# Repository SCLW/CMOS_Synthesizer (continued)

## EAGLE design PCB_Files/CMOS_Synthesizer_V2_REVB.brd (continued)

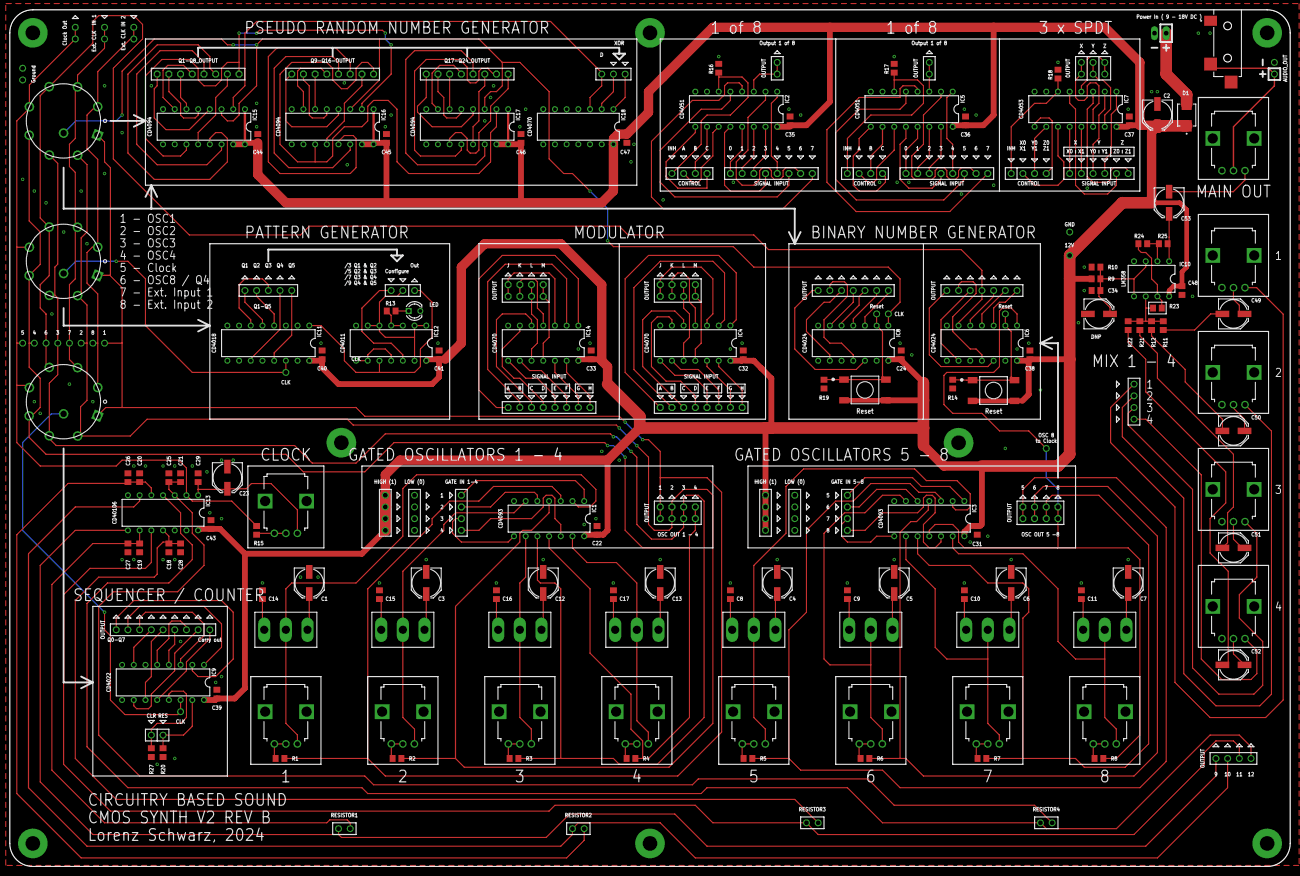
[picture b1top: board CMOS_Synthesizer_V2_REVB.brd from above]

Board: 2 copper layers, 278.0 x 186.0 mm, 218 parts (0 on the bottom side), 214 nets.

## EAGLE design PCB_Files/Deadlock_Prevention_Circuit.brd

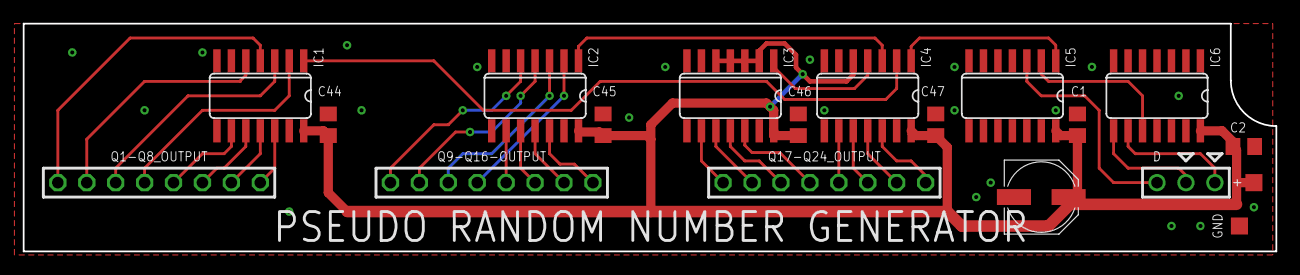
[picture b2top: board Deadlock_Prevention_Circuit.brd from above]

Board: 2 copper layers, 110.0 x 20.0 mm, 20 parts (0 on the bottom side), 34 nets.

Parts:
12V: TPTP15SQ; TP15SQ
C1, C2, C44, C45, C46, C47: 0.1uF; C0805
C3: PANASONIC_D
DATA_IN: 1X01
GND: TPTP15SQ; TP15SQ
IC1, IC2, IC3, IC4: 4068D; SO14
IC5: 4070D; SO14
IC6: 4077D; SO14
JP2: 1X02
Q1-Q8_OUTPUT, Q9-Q16-OUTPUT, Q17-Q24_OUTPUT: 1X08

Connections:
+12V: 12V.TP, C1.1, C2.1, C3.+, C44.1, C45.1, C46.1, C47.1, IC1.14, IC2.14, IC3.2, IC3.3, IC3.4, IC3.5, IC3.14, IC4.5, IC4.14, IC5.14, IC6.14
GND: C1.2, C2.2, C3.-, C44.2, C45.2, C46.2, C47.2, GND.TP, IC1.7, IC2.7, IC3.7, IC4.7, IC5.5, IC5.6, IC5.7, IC5.8, IC5.9, IC5.12, IC5.13, IC6.1, IC6.2, IC6.5, IC6.6, IC6.7, IC6.12, IC6.13
unnamed: IC1.12, Q1-Q8_OUTPUT.8
unnamed: IC6.9, JP2.1
unnamed: IC1.1, IC4.2
unnamed: IC2.1, IC4.3
unnamed: IC3.1, IC4.4
unnamed: IC6.8, JP2.2
unnamed: IC5.2, IC6.10
unnamed: DATA_IN.1, IC5.3
unnamed: IC4.1, IC5.1
unnamed: IC1.5, Q1-Q8_OUTPUT.2
unnamed: IC1.4, Q1-Q8_OUTPUT.1
unnamed: IC1.3, Q1-Q8_OUTPUT.3
unnamed: IC1.2, Q1-Q8_OUTPUT.4
unnamed: IC3.9, Q17-Q24_OUTPUT.1
unnamed: IC3.10, Q17-Q24_OUTPUT.2
unnamed: IC3.11, Q17-Q24_OUTPUT.3
unnamed: IC3.12, Q17-Q24_OUTPUT.4
unnamed: IC4.9, Q17-Q24_OUTPUT.5
unnamed: IC4.10, Q17-Q24_OUTPUT.6
unnamed: IC4.11, Q17-Q24_OUTPUT.7
unnamed: IC4.12, Q17-Q24_OUTPUT.8
unnamed: IC2.12, Q9-Q16-OUTPUT.8
unnamed: IC1.11, Q1-Q8_OUTPUT.7
unnamed: IC1.10, Q1-Q8_OUTPUT.6
unnamed: IC1.9, Q1-Q8_OUTPUT.5
unnamed: IC2.5, Q9-Q16-OUTPUT.1
unnamed: IC2.4, Q9-Q16-OUTPUT.2
unnamed: IC2.3, Q9-Q16-OUTPUT.3
unnamed: IC2.2, Q9-Q16-OUTPUT.4
unnamed: IC2.9, Q9-Q16-OUTPUT.5
unnamed: IC2.10, Q9-Q16-OUTPUT.6
unnamed: IC2.11, Q9-Q16-OUTPUT.7

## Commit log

2025-10-15 edit
2025-10-15 upload
2025-10-16 Add link to Circuitry-Based Sound seminar in README
    Updated the project description to include a link to the Circuitry-Based Sound seminar.
2025-10-22 Update image format for Revision A in README
2025-10-22 Fix image source path in README
    Updated image path for clarity in README.
2025-11-15 Update README with mounting hole correction details
    Correct the offset of the central mounting holes and note the need for a new base plate design.
2025-11-19 Fix punctuation in README.md
2026-04-20 compress Media images
2026-04-20 remove .DS_Store, add gitignore
2026-04-20 compress Media images, convert photo PNGs to JPEG
2026-04-20 Remove .DS_Store, add .gitignore
2026-04-20 Remove obsolete GIF reference from README
2026-04-20 Fix broken anchor link and disclaimer text
2026-05-14 Restructure repository into assets/ folder layout
2026-05-14 Fix CD4070 BOM quantity
2026-05-14 Add LICENSE, CITATION.cff, README updates
2026-05-14 Remove byline note from README
2026-05-14 Trim external links from Performances section
2026-05-14 Rewrite About section, trim Performances links
2026-05-14 Update CITATION date to 2026-05-14
2026-05-14 add deadlock-prevention BOM, clarify licensing
2026-05-14 rephrase section
2026-05-14 remove substitute header reference
2026-05-14 fix Open M Art Fair caption
2026-05-14 Update photo credit and filename for ZKM Klangdom image
2026-05-14 cleanup and BOM corrections
2026-05-14 Update README, BOM, and image assets
2026-05-15 Add photos and clean up formatting
2026-05-15 Update photos, metadata, and docs
2026-05-15 Edit revision statement
2026-05-15 Update Zenodo release notes
2026-05-15 Format event list
2026-05-15 Fill in v1.0.0 DOIs from Zenodo
